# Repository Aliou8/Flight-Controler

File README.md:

# Flight-Controler

## Description du projet 
Ce projet personnel a pour objectif de développer un contrôleur de vol basé sur un microcontrôleur ESP32, intégrant divers capteurs et actionneurs. Le développement a été réalisé au cours du mois d'août 2025, en utilisant KiCad pour la conception du PCB.

## Schema 

## Resultat

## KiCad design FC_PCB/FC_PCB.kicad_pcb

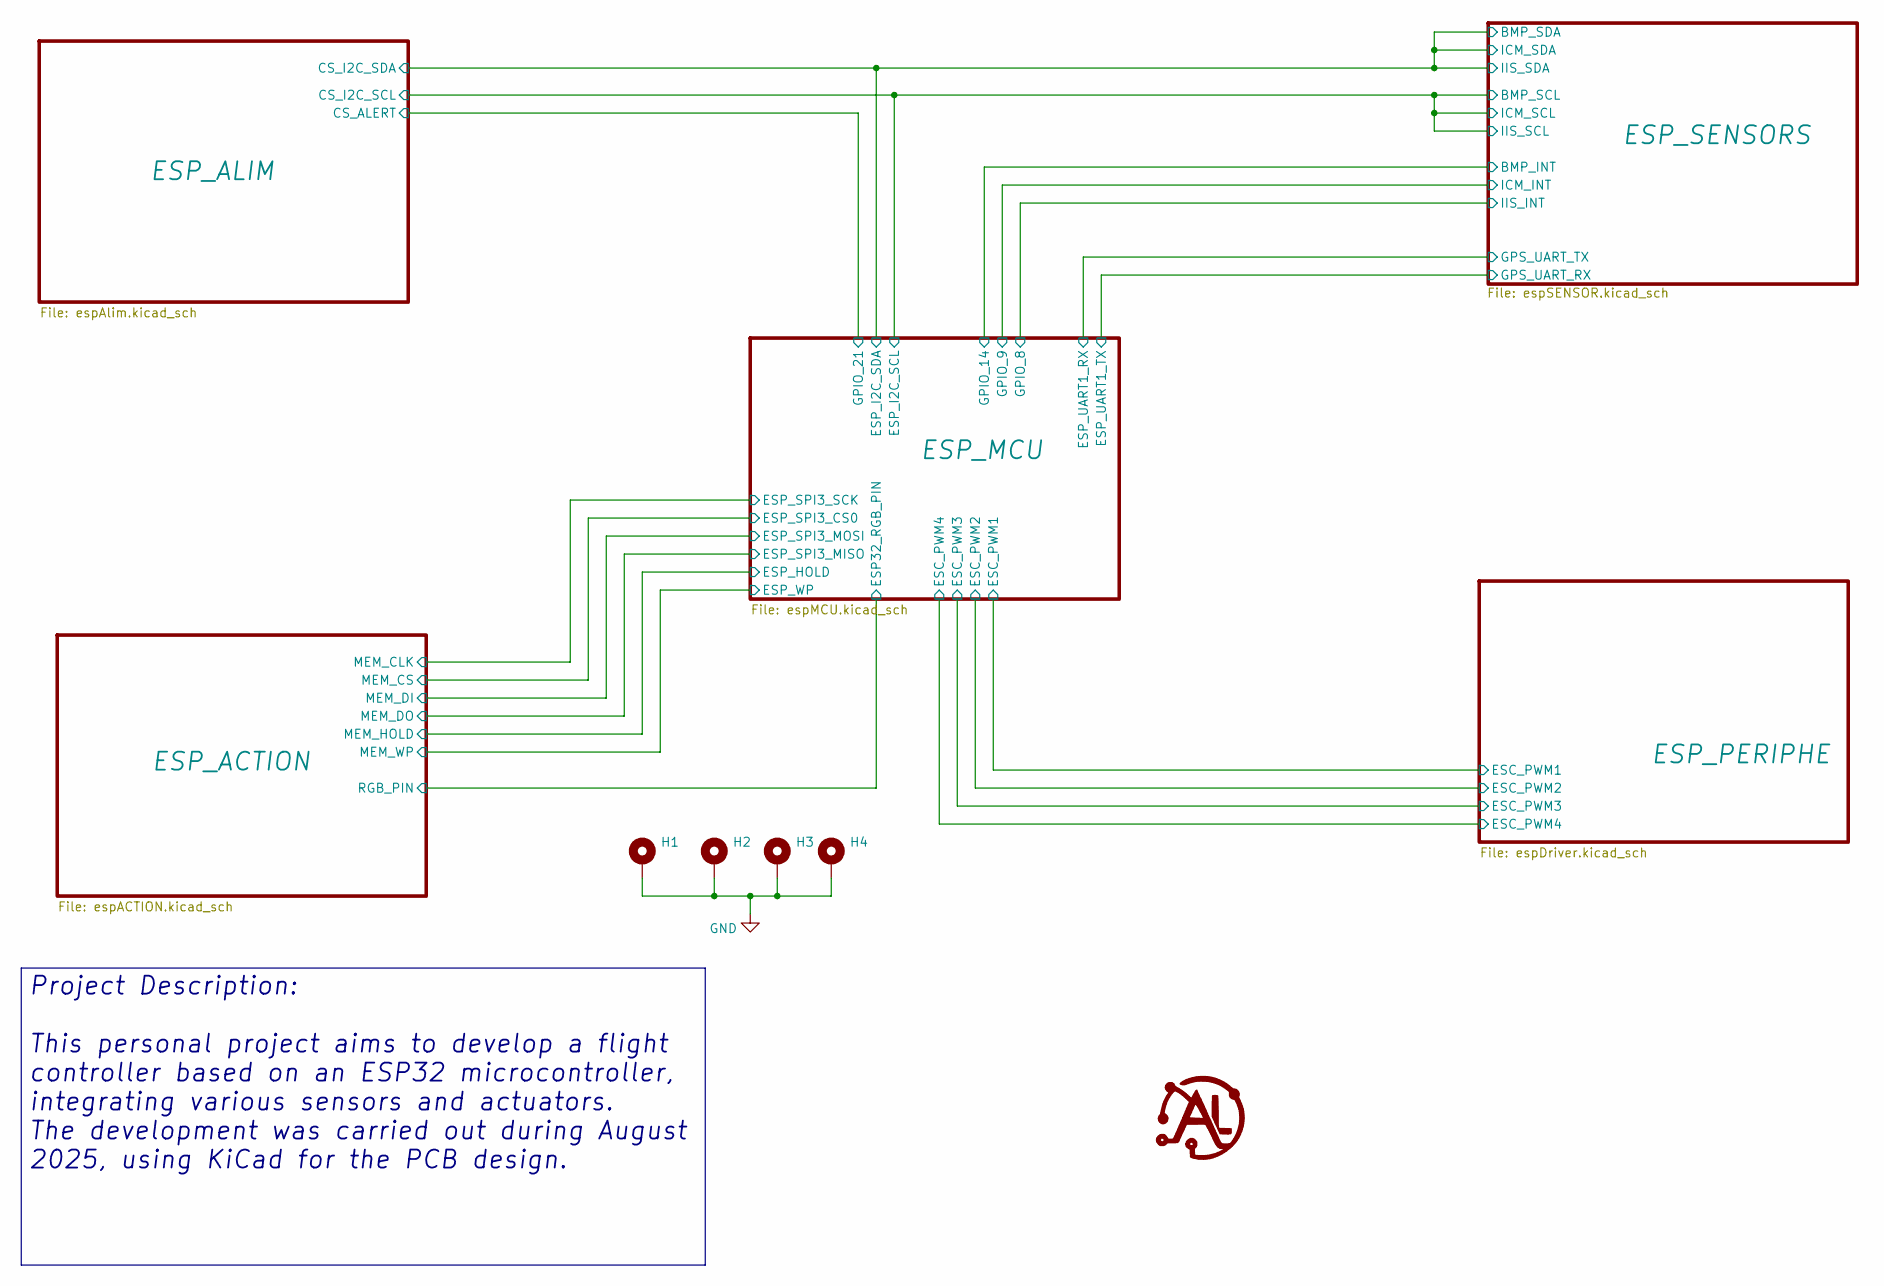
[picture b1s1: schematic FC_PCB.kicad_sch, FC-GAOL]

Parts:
H1, H2, H3, H4: MountingHole_Pad; MountingHole_2.2mm_M2_Pad_Via

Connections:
GND: H1.1, H2.1, H3.1, H4.1; also elsewhere on the board

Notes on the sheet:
Project Description: This personal project aims to develop a flight controller based on an ESP32 microcontroller, integrating various sensors and actuators. The development was carried out during August 2025, using KiCad for the PCB design.

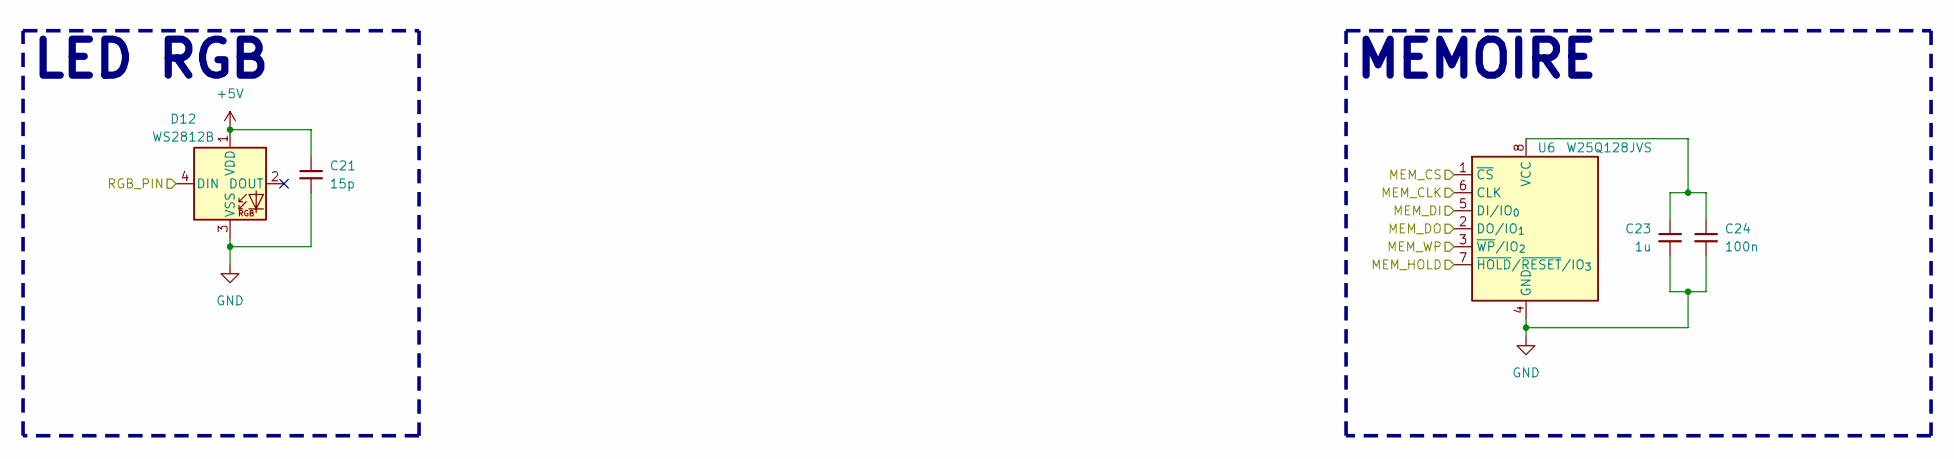
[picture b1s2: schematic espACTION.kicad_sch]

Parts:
C21: 15p; C_0603_1608Metric
C23: 1u; C_0402_1005Metric
C24: 100n; C_0402_1005Metric
D12: WS2812B; LED_WS2812B_PLCC4_5.0x5.0mm_P3.2mm
U6: W25Q128JVS; SOIC-8_5.3x5.3mm_P1.27mm

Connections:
+5V: C21.1, D12.1 (VDD); also elsewhere on the board
/ESP_ACTION/MEM_CLK: U6.6 (CLK); also elsewhere on the board
/ESP_ACTION/MEM_CS: U6.1 (~CS); also elsewhere on the board
/ESP_ACTION/MEM_DI: U6.5 (DI/IO_{0}); also elsewhere on the board
/ESP_ACTION/MEM_DO: U6.2 (DO/IO_{1}); also elsewhere on the board
/ESP_ACTION/MEM_HOLD: U6.7 (~HOLD/~RESET/IO_{3}); also elsewhere on the board
/ESP_ACTION/MEM_WP: U6.3 (~WP/IO_{2}); also elsewhere on the board
/ESP_ACTION/RGB_PIN: D12.4 (DIN); also elsewhere on the board
GND: C21.2, C23.2, C24.2, D12.3 (VSS), U6.4 (GND); also elsewhere on the board
unnamed: C23.1, C24.1, U6.8 (VCC)

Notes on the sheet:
MEMOIRE
LED RGB

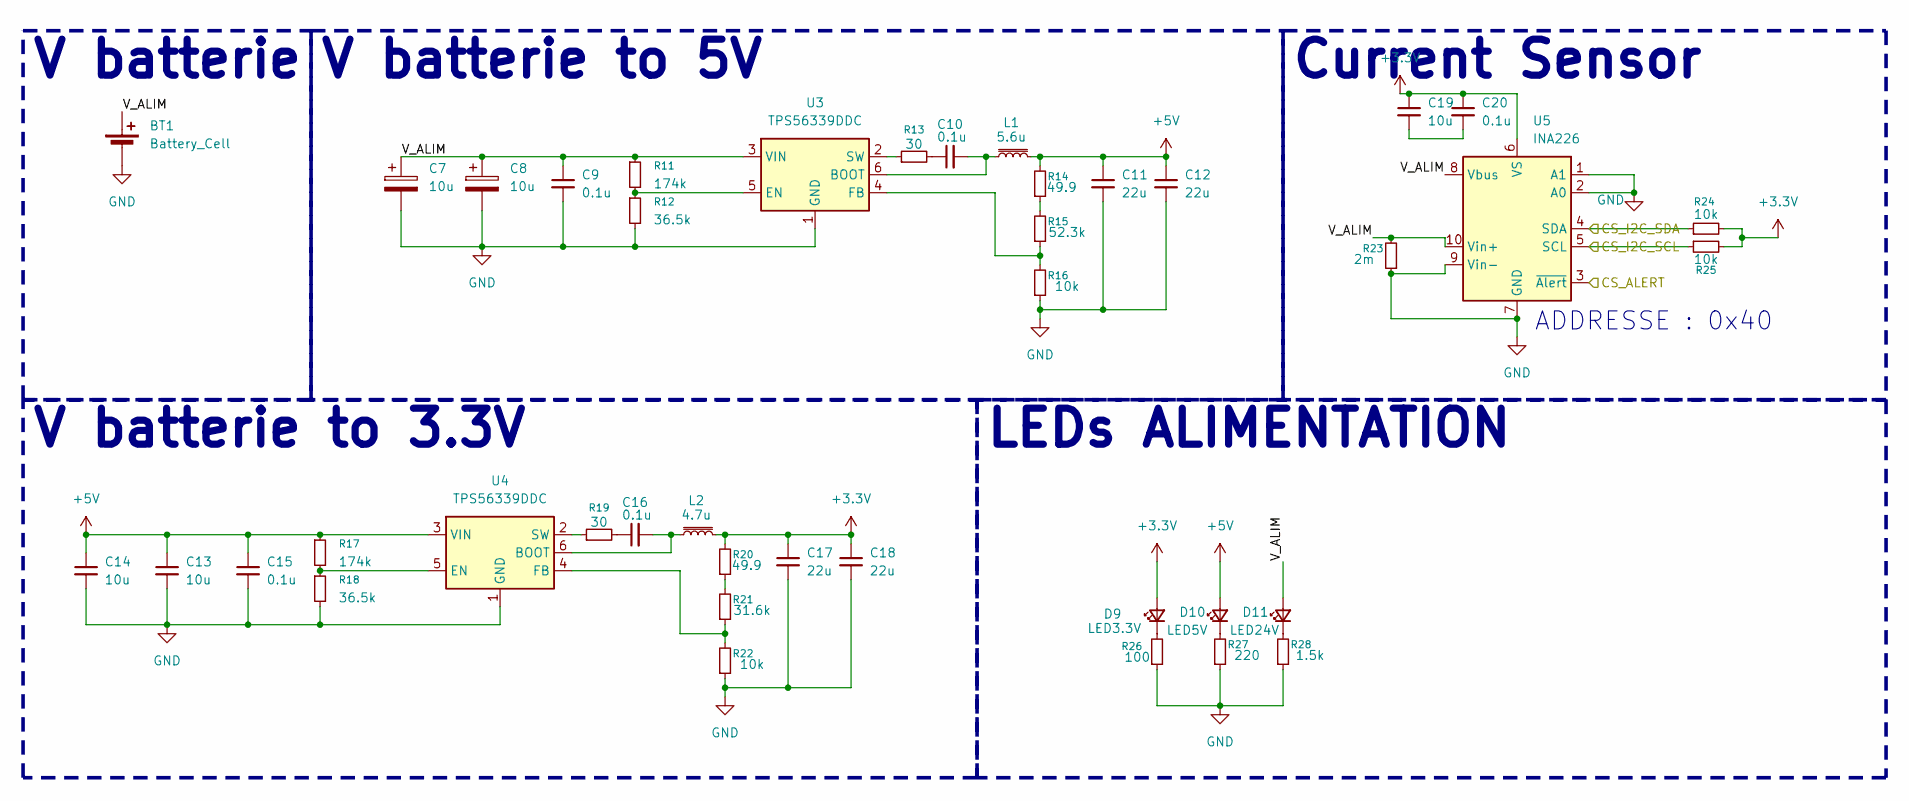
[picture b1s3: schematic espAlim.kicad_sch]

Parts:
BT1: Battery_Cell; TerminalBlock_Phoenix_PT-1,5-2-3.5-H_1x02_P3.50mm_Horizontal
C7, C8: 10u; CP_Elec_4x3
C9, C10, C15, C16, C20: 0.1u; C_0402_1005Metric
C11, C12, C17, C18: 22u; C_0603_1608Metric
C13, C14, C19: 10u; C_0402_1005Metric
D9: LED3.3V; LED_0402_1005Metric
D10: LED5V; LED_0402_1005Metric
D11: LED24V; LED_0402_1005Metric
L1: 5.6u; LSXND5050XATR47NMG
L2: 4.7u; LSXND5050XATR47NMG
R11, R17: 174k; C_0402_1005Metric
R12, R18: 36.5k; C_0402_1005Metric
R13, R19: 30; R_0603_1608Metric
R14: 49.9; R_0603_1608Metric
R15: 52.3k; C_0402_1005Metric
R16, R22, R24, R25: 10k; C_0402_1005Metric
R20: 49.9; C_0603_1608Metric
R21: 31.6k; C_0402_1005Metric
R23: 2m; R_0603_1608Metric
R26: 100; C_0402_1005Metric
R27: 220; C_0402_1005Metric
R28: 1.5k; C_0402_1005Metric
U3, U4: TPS56339DDC; SOT-23-6
U5: INA226; VSSOP-10_3x3mm_P0.5mm

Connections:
+3.3V: C17.1, C18.1, C19.1, C20.1, D9.2 (A), L2.2, R20.2, R24.2, R25.2, U5.6 (VS); also elsewhere on the board
+5V: C11.1, C12.1, C13.1, C14.1, C15.1, D10.2 (A), L1.2, R14.2, R17.1, U4.3 (VIN); also elsewhere on the board
/ESP_ALIM/CS_ALERT: U5.3 (~Alert); also elsewhere on the board
/ESP_ALIM/CS_I2C_SCL: R25.1, U5.5 (SCL); also elsewhere on the board
/ESP_ALIM/CS_I2C_SDA: R24.1, U5.4 (SDA); also elsewhere on the board
/ESP_ALIM/V_ALIM: BT1.1 (+), C7.1, C8.1, C9.1, D11.2 (A), R11.1, R23.2, U3.3 (VIN), U5.8 (Vbus), U5.10 (Vin+)
GND: BT1.2 (-), C7.2, C8.2, C9.2, C11.2, C12.2, C13.2, C14.2, C15.2, C17.2, C18.2, R12.2, R16.1, R18.2, R22.1, R23.1, R26.1, R27.1, R28.1, U3.1 (GND), U4.1 (GND), U5.1 (A1), U5.2 (A0), U5.7 (GND), U5.9 (Vin-); also elsewhere on the board
unnamed: C10.1, R13.2
unnamed: C16.1, R19.2
unnamed: C19.2, C20.2
unnamed: D9.1 (K), R26.2
unnamed: D10.1 (K), R27.2
unnamed: D11.1 (K), R28.2
unnamed: R14.1, R15.2
unnamed: R20.1, R21.2
unnamed: C10.2, L1.1, U3.6 (BOOT)
unnamed: R11.2, R12.1, U3.5 (EN)
unnamed: R15.1, R16.2, U3.4 (FB)
unnamed: R13.1, U3.2 (SW)
unnamed: C16.2, L2.1, U4.6 (BOOT)
unnamed: R17.2, R18.1, U4.5 (EN)
unnamed: R21.1, R22.2, U4.4 (FB)
unnamed: R19.1, U4.2 (SW)

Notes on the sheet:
ADDRESSE : 0x40
V batterie to 3.3V
V batterie to 5V
LEDs ALIMENTATION
V batterie
Current Sensor

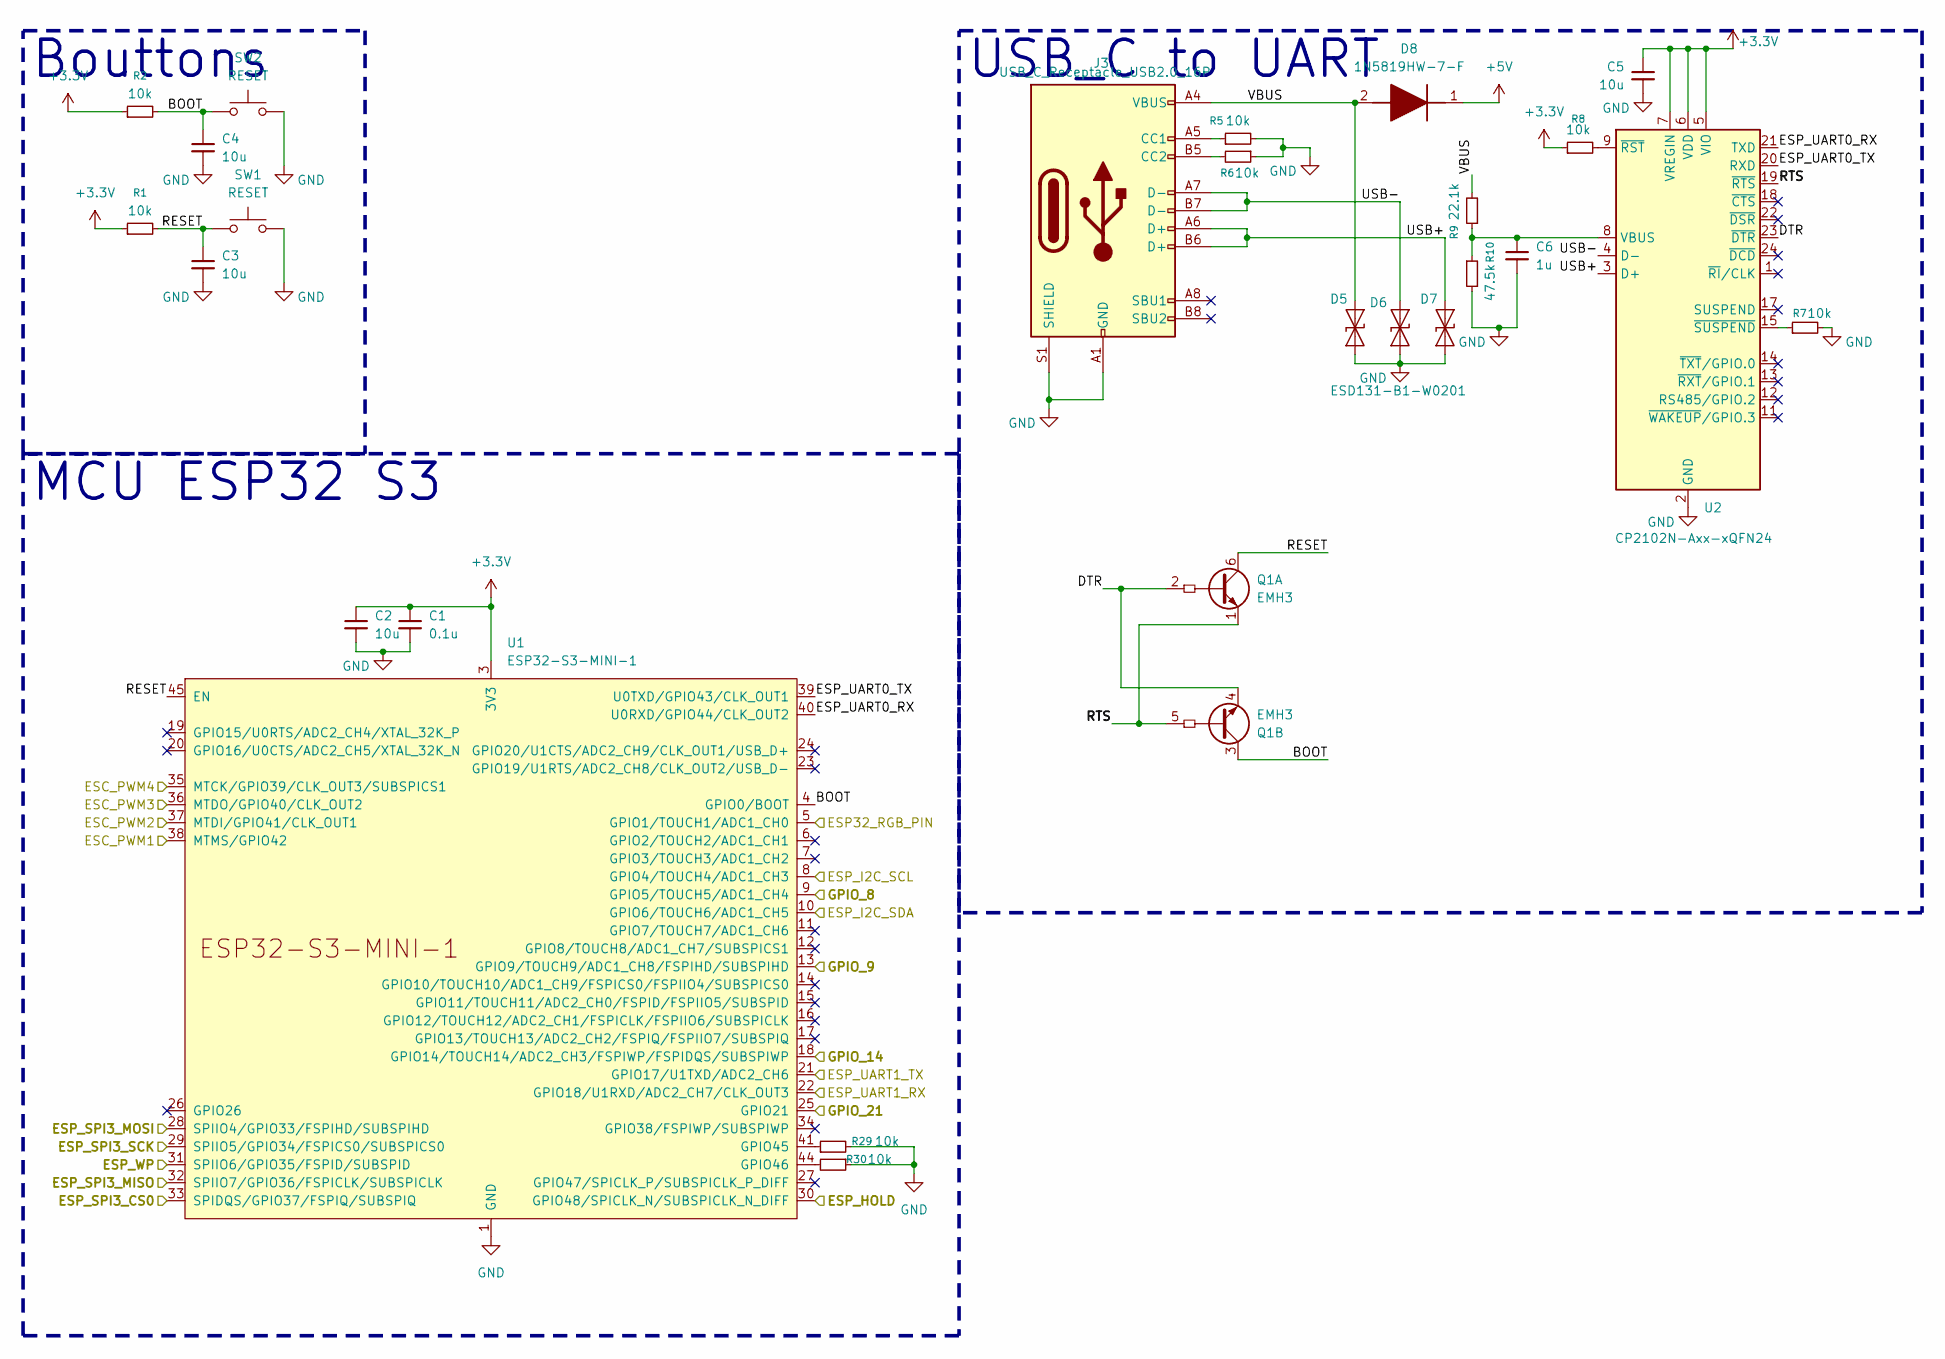
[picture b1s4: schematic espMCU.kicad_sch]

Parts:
C1: 0.1u; C_0402_1005Metric
C2, C3, C4, C5: 10u; C_0402_1005Metric
C6: 1u; C_0402_1005Metric
D5, D6, D7: ESD131-B1-W0201; Infineon_SG-WLL-2-3_0.58x0.28_P0.36mm
D8: 1N5819HW-7-F; D_SOD-123; Mouser Part Number 621-1N5819HW-F
J3: USB_C_Receptacle_USB2.0_16P; USB_C_Receptacle_GCT_USB4105-xx-A_16P_TopMnt_Horizontal
Q1: EMH3; SOT-563
R1, R2, R5, R6, R7, R8, R29, R30: 10k; C_0402_1005Metric
R9: 22.1k; C_0402_1005Metric
R10: 47.5k; C_0402_1005Metric
SW1, SW2: RESET; SW_SPST_EVQP2_MiddlePushTravel_H2.5mm
U1: ESP32-S3-MINI-1
U2: CP2102N-Axx-xQFN24; QFN-24-1EP_4x4mm_P0.5mm_EP2.6x2.6mm

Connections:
+3.3V: C1.1, C2.1, C5.1, R1.1, R2.1, R8.1, U1.3 (3V3), U2.5 (VIO), U2.6 (VDD), U2.7 (VREGIN); also elsewhere on the board
+5V: D8.1 (K); also elsewhere on the board
/ESP_ACTION/MEM_CLK: U1.29 (SPIIO5/GPIO34/FSPICS0/SUBSPICS0); also elsewhere on the board
/ESP_ACTION/MEM_CS: U1.33 (SPIDQS/GPIO37/FSPIQ/SUBSPIQ); also elsewhere on the board
/ESP_ACTION/MEM_DI: U1.28 (SPIIO4/GPIO33/FSPIHD/SUBSPIHD); also elsewhere on the board
/ESP_ACTION/MEM_DO: U1.32 (SPIIO7/GPIO36/FSPICLK/SUBSPICLK); also elsewhere on the board
/ESP_ACTION/MEM_HOLD: U1.30 (GPIO48/SPICLK_N/SUBSPICLK_N_DIFF); also elsewhere on the board
/ESP_ACTION/MEM_WP: U1.31 (SPIIO6/GPIO35/FSPID/SUBSPID); also elsewhere on the board
/ESP_ACTION/RGB_PIN: U1.5 (GPIO1/TOUCH1/ADC1_CH0); also elsewhere on the board
/ESP_ALIM/CS_ALERT: U1.25 (GPIO21); also elsewhere on the board
/ESP_ALIM/CS_I2C_SCL: U1.8 (GPIO4/TOUCH4/ADC1_CH3); also elsewhere on the board
/ESP_ALIM/CS_I2C_SDA: U1.10 (GPIO6/TOUCH6/ADC1_CH5); also elsewhere on the board
/ESP_MCU/BOOT: C4.1, Q1.3 (C2), R2.2, SW2.1, U1.4 (GPIO0/BOOT)
/ESP_MCU/DTR: Q1.2 (B1), Q1.4 (E2), U2.23 (~DTR)
/ESP_MCU/ESC_PWM1: U1.38 (MTMS/GPIO42); also elsewhere on the board
/ESP_MCU/ESC_PWM2: U1.37 (MTDI/GPIO41/CLK_OUT1); also elsewhere on the board
/ESP_MCU/ESC_PWM3: U1.36 (MTDO/GPIO40/CLK_OUT2); also elsewhere on the board
/ESP_MCU/ESC_PWM4: U1.35 (MTCK/GPIO39/CLK_OUT3/SUBSPICS1); also elsewhere on the board
/ESP_MCU/ESP_UART0_RX: U1.40 (U0RXD/GPIO44/CLK_OUT2), U2.21 (TXD)
/ESP_MCU/ESP_UART0_TX: U1.39 (U0TXD/GPIO43/CLK_OUT1), U2.20 (RXD)
/ESP_MCU/ESP_UART1_RX: U1.22 (GPIO18/U1RXD/ADC2_CH7/CLK_OUT3); also elsewhere on the board
/ESP_MCU/ESP_UART1_TX: U1.21 (GPIO17/U1TXD/ADC2_CH6); also elsewhere on the board
/ESP_MCU/GPIO_8: U1.9 (GPIO5/TOUCH5/ADC1_CH4); also elsewhere on the board
/ESP_MCU/GPIO_9: U1.13 (GPIO9/TOUCH9/ADC1_CH8/FSPIHD/SUBSPIHD); also elsewhere on the board
/ESP_MCU/GPIO_14: U1.18 (GPIO14/TOUCH14/ADC2_CH3/FSPIWP/FSPIDQS/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); also elsewhere on the board
/ESP_MCU/RESET: C3.1, Q1.6 (C1), R1.2, SW1.1, U1.45 (EN)
/ESP_MCU/RTS: Q1.1 (E1), Q1.5 (B2), U2.19 (~RTS)
/ESP_MCU/USB+: D7.1 (A1), J3.A6 (D+), J3.B6 (D+), U2.3 (D+)
/ESP_MCU/USB-: D6.1 (A1), J3.A7 (D-), J3.B7 (D-), U2.4 (D-)
/ESP_MCU/VBUS: D5.1 (A1), D8.2 (A), J3.A4 (VBUS), J3.A9 (VBUS), J3.B4 (VBUS), J3.B9 (VBUS), R9.2
GND: C1.2, C2.2, C3.2, C4.2, C5.2, C6.2, D5.2 (A2), D6.2 (A2), D7.2 (A2), J3.A1 (GND), J3.A12 (GND), J3.B1 (GND), J3.B12 (GND), J3.S1 (SHIELD), R5.2, R6.1, R7.2, R10.2, R29.2, R30.1, SW1.2, SW2.2, U1.1 (GND), U1.2 (GND), U1.42 (GND), U1.43 (GND), U1.46 (GND), U1.47 (GND), U1.48 (GND), U1.49 (GND), U1.50 (GND), U1.51 (GND), U1.52 (GND), U1.53 (GND), U1.54 (GND), U1.55 (GND), U1.56 (GND), U1.57 (GND), U1.58 (GND), U1.59 (GND), U1.60 (GND), U1.61 (GND), U1.62 (GND), U1.63 (GND), U1.64 (GND), U1.65 (GND), U2.2 (GND), U2.25 (GND); also elsewhere on the board
unnamed: J3.A5 (CC1), R5.1
unnamed: J3.B5 (CC2), R6.2
unnamed: R29.1, U1.41 (GPIO45)
unnamed: R30.2, U1.44 (GPIO46)
unnamed: C6.1, R9.1, R10.1, U2.8 (VBUS)
unnamed: R8.2, U2.9 (~RST)
unnamed: R7.1, U2.15 (~SUSPEND)

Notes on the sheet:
USB_C to UART
Bouttons
MCU ESP32 S3

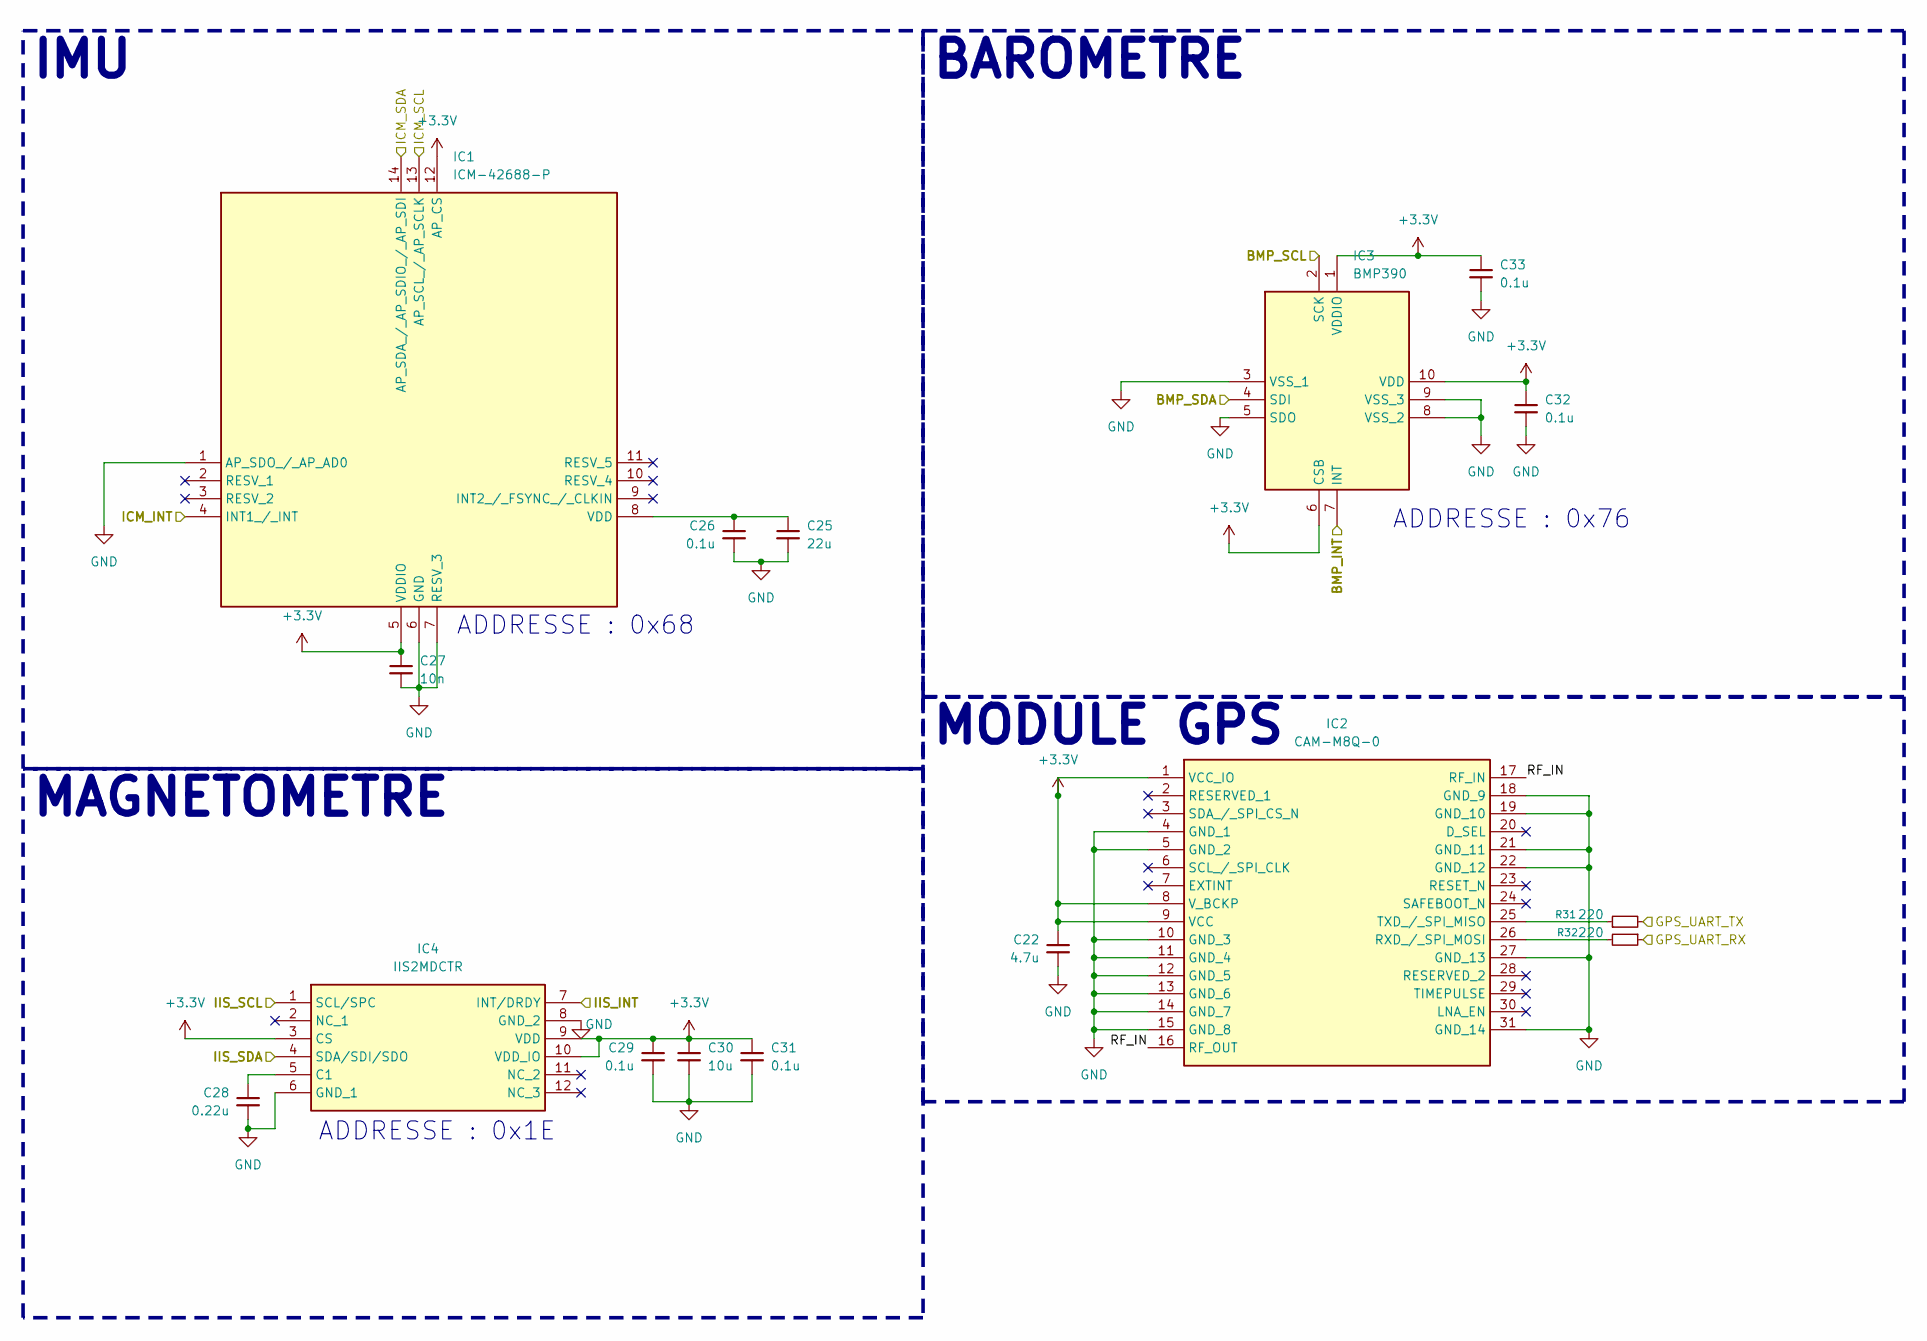
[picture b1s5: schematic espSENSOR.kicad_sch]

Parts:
C22: 4.7u; C_0603_1608Metric
C25: 22u; C_0603_1608Metric
C26, C29, C31, C32, C33: 0.1u; C_0402_1005Metric
C27: 10n; C_0402_1005Metric
C28: 0.22u; C_0402_1005Metric
C30: 10u; C_0402_1005Metric
IC1: ICM-42688-P; IIM42352; Mouser Part Number 410-ICM-42688-P
IC2: CAM-M8Q-0; CAMM8Q0; Mouser Part Number 377-CAM-M8Q-0
IC3: BMP390; Mouser Part Number 262-BMP390
IC4: IIS2MDCTR; Mouser Part Number 511-IIS2MDCTR
R31, R32: 220; C_0402_1005Metric

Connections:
+3.3V: C22.1, C27.1, C29.1, C30.1, C31.1, C32.1, C33.1, IC1.5 (VDDIO), IC1.12 (AP_CS), IC2.1 (VCC_IO), IC2.8 (V_BCKP), IC2.9 (VCC), IC3.1 (VDDIO), IC3.6 (CSB), IC3.10 (VDD), IC4.3 (CS), IC4.9 (VDD), IC4.10 (VDD_IO); also elsewhere on the board
/ESP_ALIM/CS_I2C_SCL: IC1.13 (AP_SCL_/_AP_SCLK), IC3.2 (SCK), IC4.1 (SCL/SPC); also elsewhere on the board
/ESP_ALIM/CS_I2C_SDA: IC1.14 (AP_SDA_/_AP_SDIO_/_AP_SDI), IC3.4 (SDI), IC4.4 (SDA/SDI/SDO); also elsewhere on the board
/ESP_MCU/ESP_UART1_RX: R31.2; also elsewhere on the board
/ESP_MCU/ESP_UART1_TX: R32.1; also elsewhere on the board
/ESP_MCU/GPIO_8: IC4.7 (INT/DRDY); also elsewhere on the board
/ESP_MCU/GPIO_9: IC1.4 (INT1_/_INT); also elsewhere on the board
/ESP_MCU/GPIO_14: IC3.7 (INT); also elsewhere on the board
/ESP_SENSORS/RF_IN: IC2.16 (RF_OUT), IC2.17 (RF_IN)
GND: C22.2, C25.2, C26.2, C27.2, C28.2, C29.2, C30.2, C31.2, C32.2, C33.2, IC1.1 (AP_SDO_/_AP_AD0), IC1.6 (GND), IC1.7 (RESV_3), IC2.4 (GND_1), IC2.5 (GND_2), IC2.10 (GND_3), IC2.11 (GND_4), IC2.12 (GND_5), IC2.13 (GND_6), IC2.14 (GND_7), IC2.15 (GND_8), IC2.18 (GND_9), IC2.19 (GND_10), IC2.21 (GND_11), IC2.22 (GND_12), IC2.27 (GND_13), IC2.31 (GND_14), IC3.3 (VSS_1), IC3.5 (SDO), IC3.8 (VSS_2), IC3.9 (VSS_3), IC4.6 (GND_1), IC4.8 (GND_2); also elsewhere on the board
unnamed: C25.1, C26.1, IC1.8 (VDD)
unnamed: IC2.26 (RXD_/_SPI_MOSI), R32.2
unnamed: IC2.25 (TXD_/_SPI_MISO), R31.1
unnamed: C28.1, IC4.5 (C1)

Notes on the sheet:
ADDRESSE : 0x76
ADDRESSE : 0x68
ADDRESSE : 0x1E
MODULE GPS
MAGNETOMETRE
BAROMETRE
IMU

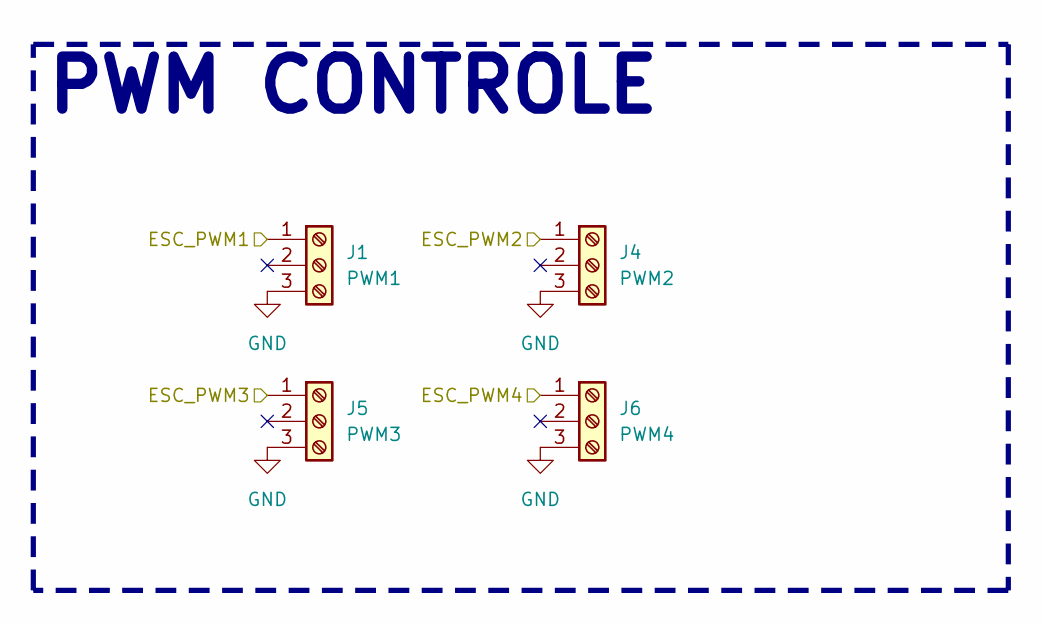
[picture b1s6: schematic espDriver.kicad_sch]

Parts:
J1: PWM1; JST_EH_B3B-EH-A_1x03_P2.50mm_Vertical
J4: PWM2; JST_EH_B3B-EH-A_1x03_P2.50mm_Vertical
J5: PWM3; JST_EH_B3B-EH-A_1x03_P2.50mm_Vertical
J6: PWM4; JST_EH_B3B-EH-A_1x03_P2.50mm_Vertical

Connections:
/ESP_MCU/ESC_PWM1: J1.1; also elsewhere on the board
/ESP_MCU/ESC_PWM2: J4.1; also elsewhere on the board
/ESP_MCU/ESC_PWM3: J5.1; also elsewhere on the board
/ESP_MCU/ESC_PWM4: J6.1; also elsewhere on the board
GND: J1.3, J4.3, J5.3, J6.3; also elsewhere on the board

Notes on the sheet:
PWM CONTROLE

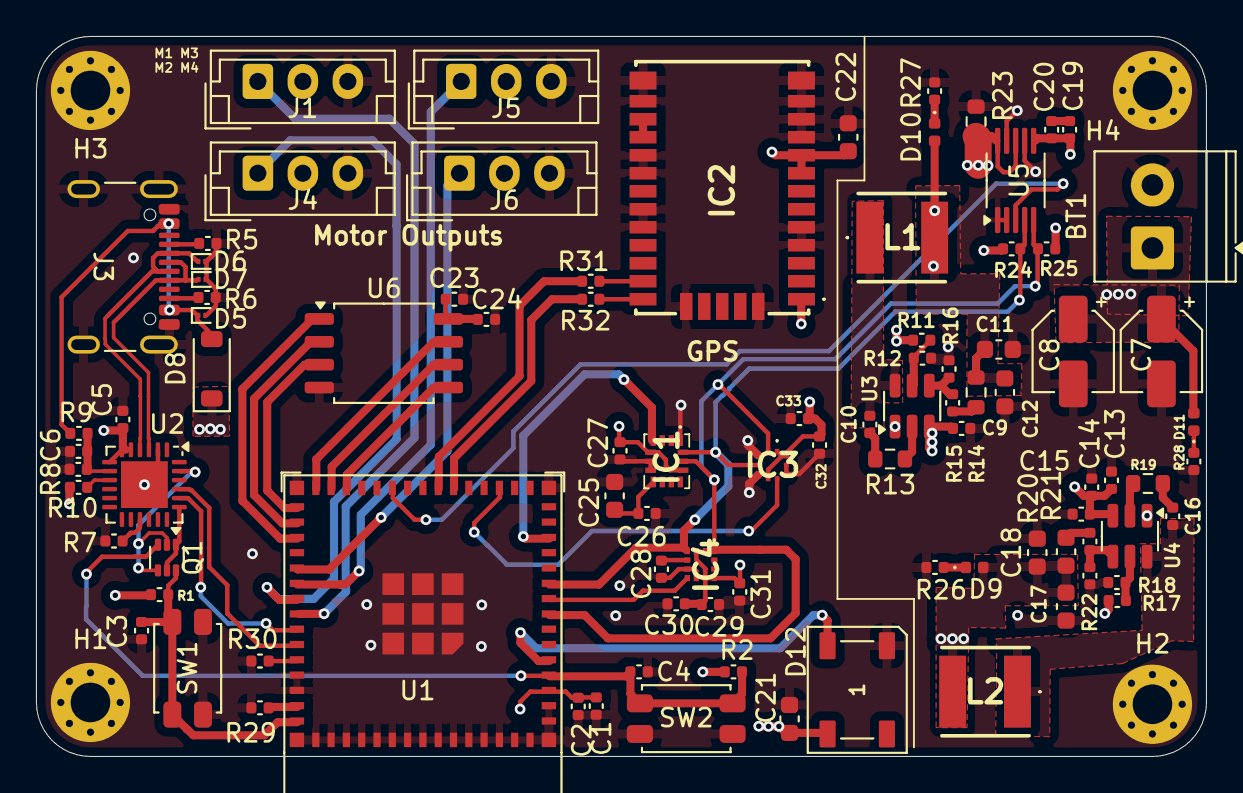
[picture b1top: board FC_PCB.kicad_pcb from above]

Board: 4 copper layers, 65.0 x 40.0 mm, 96 parts (0 on the bottom side), 61 nets.

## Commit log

2025-08-13 Commit final hard
2025-08-13 Last hard
